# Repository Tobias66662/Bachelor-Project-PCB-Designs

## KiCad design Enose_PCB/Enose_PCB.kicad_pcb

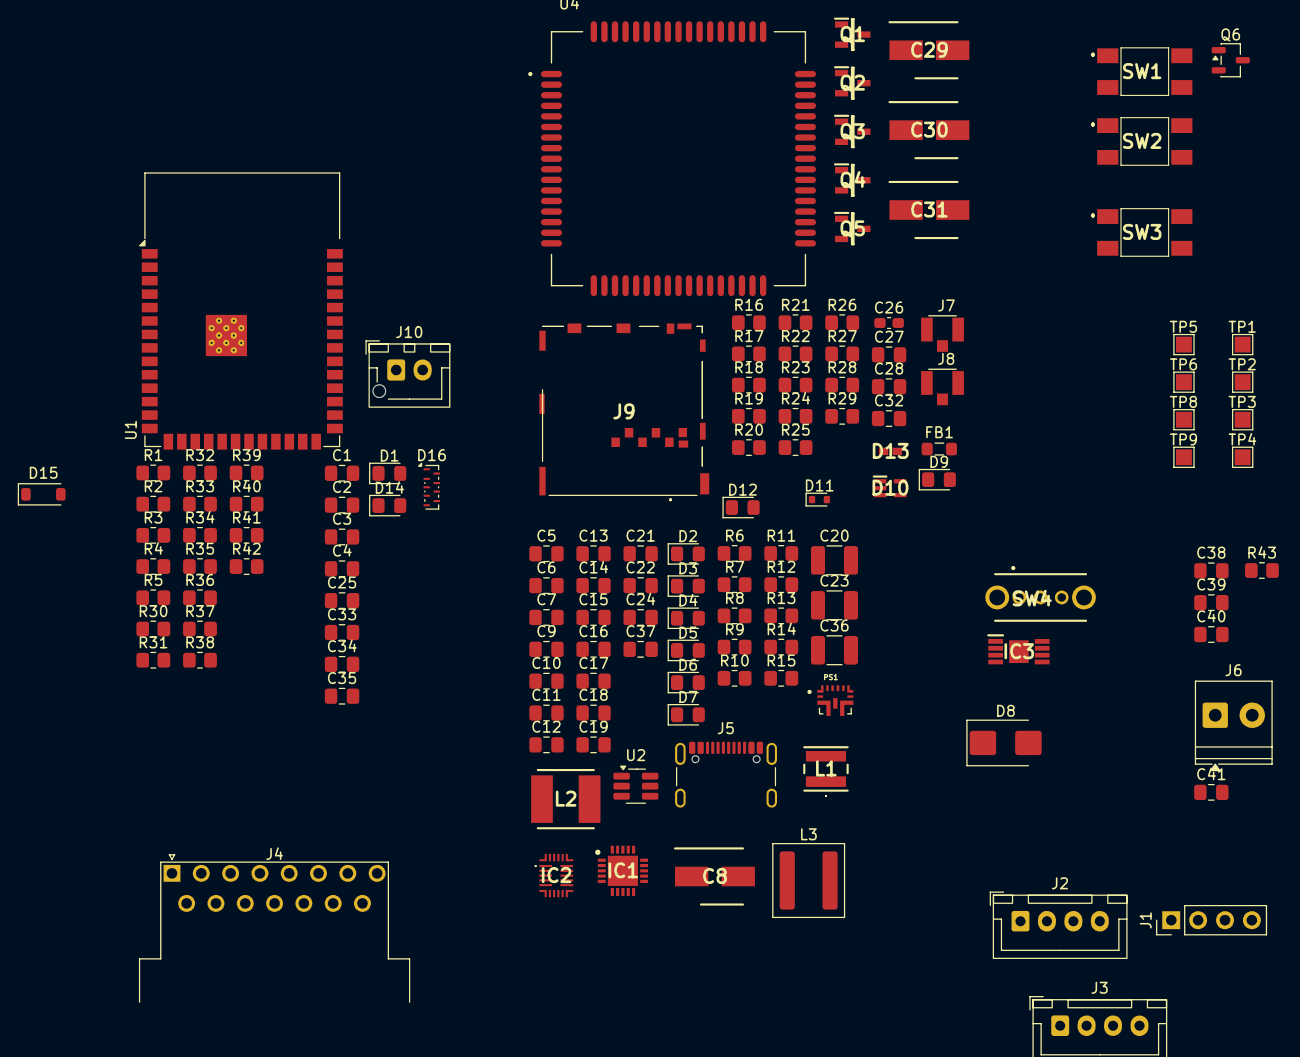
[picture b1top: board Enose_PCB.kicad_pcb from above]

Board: 2 copper layers, 139 parts (0 on the bottom side), 88 nets, no tracks yet.

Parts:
C1, C4, C28: 1u; C_0805_2012Metric_Pad1.18x1.45mm_HandSolder
C2: 22u; C_0805_2012Metric_Pad1.18x1.45mm_HandSolder
C3: 0.1u; C_0805_2012Metric_Pad1.18x1.45mm_HandSolder
C5, C6, C9, C10, C21, C24, C37: 22uF; C_0805_2012Metric_Pad1.18x1.45mm_HandSolder
C7, C11, C13, C17: 10uF; C_0805_2012Metric_Pad1.18x1.45mm_HandSolder
C8: 100uF; CAPAE530X610N
C12, C15: 0.1uF; C_0805_2012Metric_Pad1.18x1.45mm_HandSolder
C14: 22nF; C_0805_2012Metric_Pad1.18x1.45mm_HandSolder
C16, C22, C41: 2.2uF; C_0805_2012Metric_Pad1.18x1.45mm_HandSolder
C18, C38: 1uF; C_0805_2012Metric_Pad1.18x1.45mm_HandSolder
C19: 5.6nF; C_0805_2012Metric_Pad1.18x1.45mm_HandSolder
C20, C23, C36: 22uF; C_1210_3225Metric_Pad1.33x2.70mm_HandSolder
C25, C33, C34, C35, C40: 100nF; C_0805_2012Metric_Pad1.18x1.45mm_HandSolder
C26: 33p; C_0603_1608Metric_Pad1.08x0.95mm_HandSolder
C27, C32: 100n; C_0805_2012Metric_Pad1.18x1.45mm_HandSolder
C29, C30, C31: 100u; CAPAE530X610N
C39: 1500pF; C_0805_2012Metric_Pad1.18x1.45mm_HandSolder
D1, D14: LED Amber; LED_0805_2012Metric_Pad1.15x1.40mm_HandSolder
D2, D3, D9, D12: LED; LED_0805_2012Metric_Pad1.15x1.40mm_HandSolder
D4, D5: LED GREEN; LED_0805_2012Metric_Pad1.15x1.40mm_HandSolder
D6, D7: Amber LED; LED_0805_2012Metric_Pad1.15x1.40mm_HandSolder
D8: SMBJ18A-E3/52; D_SMB
D10: ESDALC6V1W5; SOT65P210X110-5N
D11: ESD5Z5.0T1G; D_SOD-523
D13: 0402ESDA-AEC1; 0402ESDAAEC1
D15: 1N5819; D_SOD-123
D16: DT1240A-08LP3810; UDFN-9_1.0x3.8mm_P0.5mm
FB1: MPZ2012S601AT000; L_0805_2012Metric_Pad1.05x1.20mm_HandSolder
IC1: ISL91127IRNZ-T7A; QFN50P400X400X100-21N
IC2: MP2722GRH-0000-Z; MP2722GRH0000Z
IC3: TPS22958DGNR; SOP65P490X110-9N
J1: Conn_01x04_Pin; PinHeader_1x04_P2.54mm_Vertical
J2, J3: Conn_01x04_Pin; JST_XH_B4B-XH-A_1x04_P2.50mm_Vertical
J4: DA15_Pins; DSUB-15_Pins_Horizontal_P2.77x2.84mm_EdgePinOffset9.40mm
J5: USB_C_Receptacle_USB2.0_16P; USB_C_Receptacle_GCT_USB4105-xx-A_16P_TopMnt_Horizontal
J6: Battery Terminal; TerminalBlock_Phoenix_PT-1,5-2-3.5-H_1x02_P3.50mm_Horizontal
J7, J8: U.FL-R-SMT_01_; HRS_U.FL-R-SMT_01_
J9: 2229333-2; 22293332
J10: Fan; JST_XH_B2B-XH-AM_1x02_P2.50mm_Vertical
L1: 1uH; SRP4030FA1R0M
L2: 1uH; INDPM5355X310N
L3: 4.7uH; L_Coilcraft_XAL6060-XXX
PS1: TPS61288LRQQR; CONV_TPS61288LRQQR
Q1, Q2, Q3, Q4, Q5: Q_NPN; SOT96P237X111-3N
Q6: NMOS; SOT-23-3
R1, R2, R3, R20, R30, R31, R32, R33: 10k; R_0805_2012Metric_Pad1.20x1.40mm_HandSolder
R4, R5, R8: 390; R_0805_2012Metric_Pad1.20x1.40mm_HandSolder
R6: 1k; R_0805_2012Metric_Pad1.20x1.40mm_HandSolder
R7, R25, R29: 680; R_0805_2012Metric_Pad1.20x1.40mm_HandSolder
R9: 6.8k; R_0805_2012Metric_Pad1.20x1.40mm_HandSolder
R10: 10k(1%); R_0805_2012Metric_Pad1.20x1.40mm_HandSolder
R11: 12k; R_0805_2012Metric_Pad1.20x1.40mm_HandSolder
R12: 288k; R_0805_2012Metric_Pad1.20x1.40mm_HandSolder
R13: 75k; R_0805_2012Metric_Pad1.20x1.40mm_HandSolder
R14, R15: 510; R_0805_2012Metric_Pad1.20x1.40mm_HandSolder
R16, R19, R21, R27: 4.7k; R_0805_2012Metric_Pad1.20x1.40mm_HandSolder
R17, R22, R28: 47k; R_0805_2012Metric_Pad1.20x1.40mm_HandSolder
R18: 4.7; R_0805_2012Metric_Pad1.20x1.40mm_HandSolder
R23, R24, R26: 22; R_0805_2012Metric_Pad1.20x1.40mm_HandSolder
R34, R35, R36, R37, R38, R39, R40, R41, R42: 100; R_0805_2012Metric_Pad1.20x1.40mm_HandSolder
R43: 100k; R_0805_2012Metric_Pad1.20x1.40mm_HandSolder
SW1, SW2, SW3: SW_SPST; 430181038816
SW4: SW_SPDT; OS102011MA1QN1
TP1, TP2, TP3, TP4, TP5, TP6, TP8, TP9: TestPoint; TestPoint_Pad_1.5x1.5mm
U1: ESP32-S3-WROOM-1
U2: USBLC6-4SC6; SOT-23-6_Handsoldering
U4: SIM7070G; MODULE_SIM7070G

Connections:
+3V3: C1.1, C2.1, C3.2, C5.2, C6.2, C21.2, C25.2, C33.1, C34.1, C35.1, IC1.15 (FB), IC1.17 (VOUT_1), IC1.18 (VOUT_2), IC1.19 (VOUT_3), IC1.20 (VOUT_4), IC1.21 (EPAD), J1.4, J2.4, J3.4, Q6.1 (D), R1.1, R2.1, R3.1, R8.1, R31.2, R32.1, R33.2, TP1.1, U1.2 (3V3)
+15V: C20.1, C23.1, C36.1, D8.1 (A1), J4.7, J4.8, J4.15, PS1.5 (VOUT), R9.1, R11.1, TP4.1
+BATT: C7.1, C11.1, C12.1, C40.2, D9.2 (A), D11.1 (A1), D12.2 (A), FB1.2, IC1.6 (PVIN_1), IC1.7 (PVIN_2), IC1.8 (PVIN_3), IC1.9 (PVIN_4), IC1.10 (VIN), IC1.11 (EN), IC3.5 (VOUT_1), IC3.8 (VOUT_2), L3.1, PS1.7 (VIN)
+SYS: C8.1, C9.1, C10.2, C37.1, C38.2, IC2.13 (SYS), IC3.1 (VIN_1), IC3.3 (VBIAS), IC3.4 (VIN_2), L2.1, R7.1, R43.2, TP2.1
/Cellular Module/GNSS_ANT: J7.3 (SIG), U4.53 (GNSS_ANT)
/Cellular Module/NETLIGHT: R27.1, U4.52 (NETLIGHT)
/Cellular Module/RF_ANT: D13.2 (A2), J8.3 (SIG), U4.60 (RF_ANT)
/Cellular Module/SIM_CLK: R24.2, U4.32 (SIM_CLK)
/Cellular Module/SIM_DATA: R23.2, U4.31 (SIM_DATA)
/Cellular Module/SIM_RST: R26.1, U4.33 (SIM_RST)
/Cellular Module/SIM_VDD: C32.2, D10.5 (K), J9.1 (VCC), U4.30 (SIM_VDD)
/Cellular Module/STATUS: R21.1, U4.66 (STATUS)
/Cellular Module/VDD_EXT: R18.1, R19.1, R20.2, TP9.1, U4.15 (VDD_EXT)
/EN: C4.1, R1.2, R3.2, SW1.4 (B), U1.3 (EN)
/ESP_LED1: R4.1, U1.6 (IO6)
/ESP_LED2: R5.1, U1.7 (IO7)
/Fan PWM: R34.2, U1.12 (IO8)
/PWM1: R35.1, U1.17 (IO9)
/PWM2: R36.1, U1.18 (IO10)
/PWM3: R37.1, U1.19 (IO11)
/PWM4: R38.1, U1.20 (IO12)
/PWM5: R39.1, U1.21 (IO13)
/PWM6: R40.1, U1.22 (IO14)
/PWM7: R41.1, U1.8 (IO15)
/PWM8: R42.1, U1.9 (IO16)
/Power Components/BATT: C24.2, IC2.12 (BATTSNS), IC2.14 (BATT), J6.1
/Power Components/BST: C14.2, IC2.6 (BST_1), IC2.24 (BST_2)
/Power Components/CC1: IC2.1 (CC1), J5.A5 (CC1), U2.1 (I/O1)
/Power Components/CC2: IC2.22 (CC2_1), IC2.23 (CC2_2), J5.B5 (CC2), U2.3 (I/O2)
/Power Components/NTC1: IC2.10 (NTC1), R10.1, TP3.1
/Power Components/PG/NTC2: D6.1 (K), IC2.9 (PG/_NTC2)
/Power Components/STAT/IB: D7.1 (K), IC2.11 (STAT/_IB_1), IC2.25 (STAT/_IB_2)
/Power Components/VCC: C22.1, C41.1, IC2.19 (VCC), R14.1, R15.1
/Power Components/VRNTC: IC2.7 (VRNTC), R10.2
/Power Components/~RST: IC2.17 (~RST_1), IC2.26 (~RST_2), SW3.1 (A)
EN(15V): PS1.6 (EN), U1.11 (IO18)
GND: C1.2, C2.2, C3.1, C4.2, C5.1, C6.1, C7.2, C8.2, C9.2, C10.1, C11.2, C12.2, C13.2, C16.2, C17.2, C18.1, C20.2, C21.1, C22.2, C23.2, C24.1, C25.1, C26.1, C27.1, C28.1, C29.2, C30.2, C31.2, C32.1, C33.2, C34.2, C35.2, C36.2, C37.2, C38.1, C39.2, C40.1, C41.2, D1.1 (K), D2.1 (K), D3.1 (K), D4.1 (K), D5.1 (K), D8.2 (A2), D10.2 (A), D11.2 (A2), D13.1 (A1), D14.1 (K), D15.2 (A), D16.3 (A), IC1.3 (PGND), IC1.12 (MODE), IC1.13 (SGND_1), IC1.14 (SGND_2), IC2.5 (PGND), IC2.18 (AGND), IC3.6 (GND), IC3.9 (EP), J1.3, J2.3, J3.3, J4.5, J4.6, J4.13, J4.14, J5.A1 (GND), J5.A12 (GND), J5.B1 (GND), J5.B12 (GND), J5.S1 (SHIELD), J6.2, J7.1 (GND), J7.2 (GND), J8.1 (GND), J8.2 (GND), J9.4 (GND_1), J9.8 (GND_2), J9.9 (GND_3), J9.10 (GND_4), J9.11 (GND_5), J9.12 (GND_6), J9.13 (GND_7), J9.14 (GND_8), J9.15 (GND_9), J9.16 (GND_10), J9.17 (GND_11), J10.2, PS1.3 (PGND), PS1.10 (AGND), R12.2, R13.2, R17.1, R22.1, R28.1, R30.2, SW1.1 (A), SW2.1 (A), SW3.4 (B), SW4.2 (B), U1.1 (GND), U1.40 (GND), U1.41 (GND), U2.2 (GND), U4.2 (GND), U4.17 (GND__1), U4.18 (GND__2), U4.29 (GND__3), U4.39 (GND__4), U4.45 (GND__5), U4.46 (GND__6), U4.54 (GND__7), U4.58 (GND__8), U4.59 (GND__9), U4.61 (GND__10), U4.62 (GND__11), U4.63 (GND__12), U4.64 (GND__13), U4.65 (GND__14)
I2C_SCL: IC2.15 (SDA), J1.2, J2.2, J3.2, R31.1, U1.27 (IO0)
I2C_SDA: IC2.16 (SCL), J1.1, J2.1, J3.1, R32.2, U1.39 (IO1)
unnamed: C15.1, L3.2, PS1.4 (SW), PS1.9 (SW)
unnamed: C19.2, R13.1
unnamed: D1.2 (A), R4.2
unnamed: D2.2 (A), R6.2
unnamed: D3.2 (A), R7.2
unnamed: D4.2 (A), R8.2
unnamed: D5.2 (A), R9.2
unnamed: D6.2 (A), R14.2
unnamed: D7.2 (A), R15.2
unnamed: D9.1 (K), R25.1
unnamed: D12.1 (K), R29.1
unnamed: D14.2 (A), R5.2
unnamed: D15.1 (K), J10.1, Q6.3 (S)
unnamed: D16.1 (K1), J4.1, R42.2
unnamed: D16.2 (K2), J4.9, R41.2
unnamed: D16.4 (K3), J4.2, R40.2
unnamed: D16.5 (K4), J4.10, R39.2
unnamed: D16.6 (K5), J4.3, R38.2
unnamed: D16.7 (K6), J4.11 (P111), R37.2
unnamed: D16.8 (K7), J4.4, R36.2
unnamed: D16.9 (K8), J4.12, R35.2
unnamed: IC1.4 (LX1_1), IC1.5 (LX1_2), L1.2
unnamed: IC1.1 (LX2_1), IC1.2 (LX2_2), L1.1
unnamed: C13.1, IC2.3 (PMID)
unnamed: C14.1, IC2.4 (SW), L2.2
unnamed: C39.1, IC3.7 (CT)
unnamed: IC3.2 (ON), R43.1, SW4.1 (A)
unnamed: D10.3 (K), J9.3 (CLK), R24.1
unnamed: D10.1 (K), J9.6 (I/O), R23.1
unnamed: D10.4 (K), J9.2 (RST), R26.2
unnamed: C15.2, PS1.8 (BST)
unnamed: C19.1, PS1.2 (COMP)
unnamed: PS1.1 (FB), R11.2, R12.1
unnamed: C16.1, PS1.11 (VCC)
unnamed: R16.2, R17.2
unnamed: R21.2, R22.2
unnamed: R27.2, R28.2
unnamed: Q6.2 (G), R30.1, R34.1
unnamed: SW2.4 (B), U1.15 (IO3)
unnamed: TP6.1, U4.22 (DEBUG_RXD)
unnamed: TP5.1, U4.23 (DEBUG_TXD)
unnamed: C26.2, R20.1, U4.10 (UART1_RXD)
unnamed: C27.2, C28.2, C29.1, C30.1, C31.1, FB1.1, TP8.1, U4.55 (VBAT), U4.56 (VBAT__1), U4.57 (VBAT__2)
PWRKEY: R16.1, U1.10 (IO17)
UART1_TXD: R2.2, U1.36 (RXD0)
USB_D+: J5.A6 (D+), J5.B6 (D+), U1.14 (USB_D+/IO20), U2.6 (I/O4)
USB_D-: J5.A7 (D-), J5.B7 (D-), U1.13 (USB_D-/IO19), U2.4 (I/O3)
VBUS: C17.1, C18.2, IC2.2 (IN), J5.A4 (VBUS), J5.A9 (VBUS), J5.B4 (VBUS), J5.B9 (VBUS), R6.1, U2.5 (VBUS)
~INT: IC2.8 (~INT), R33.1, U1.38 (IO2)

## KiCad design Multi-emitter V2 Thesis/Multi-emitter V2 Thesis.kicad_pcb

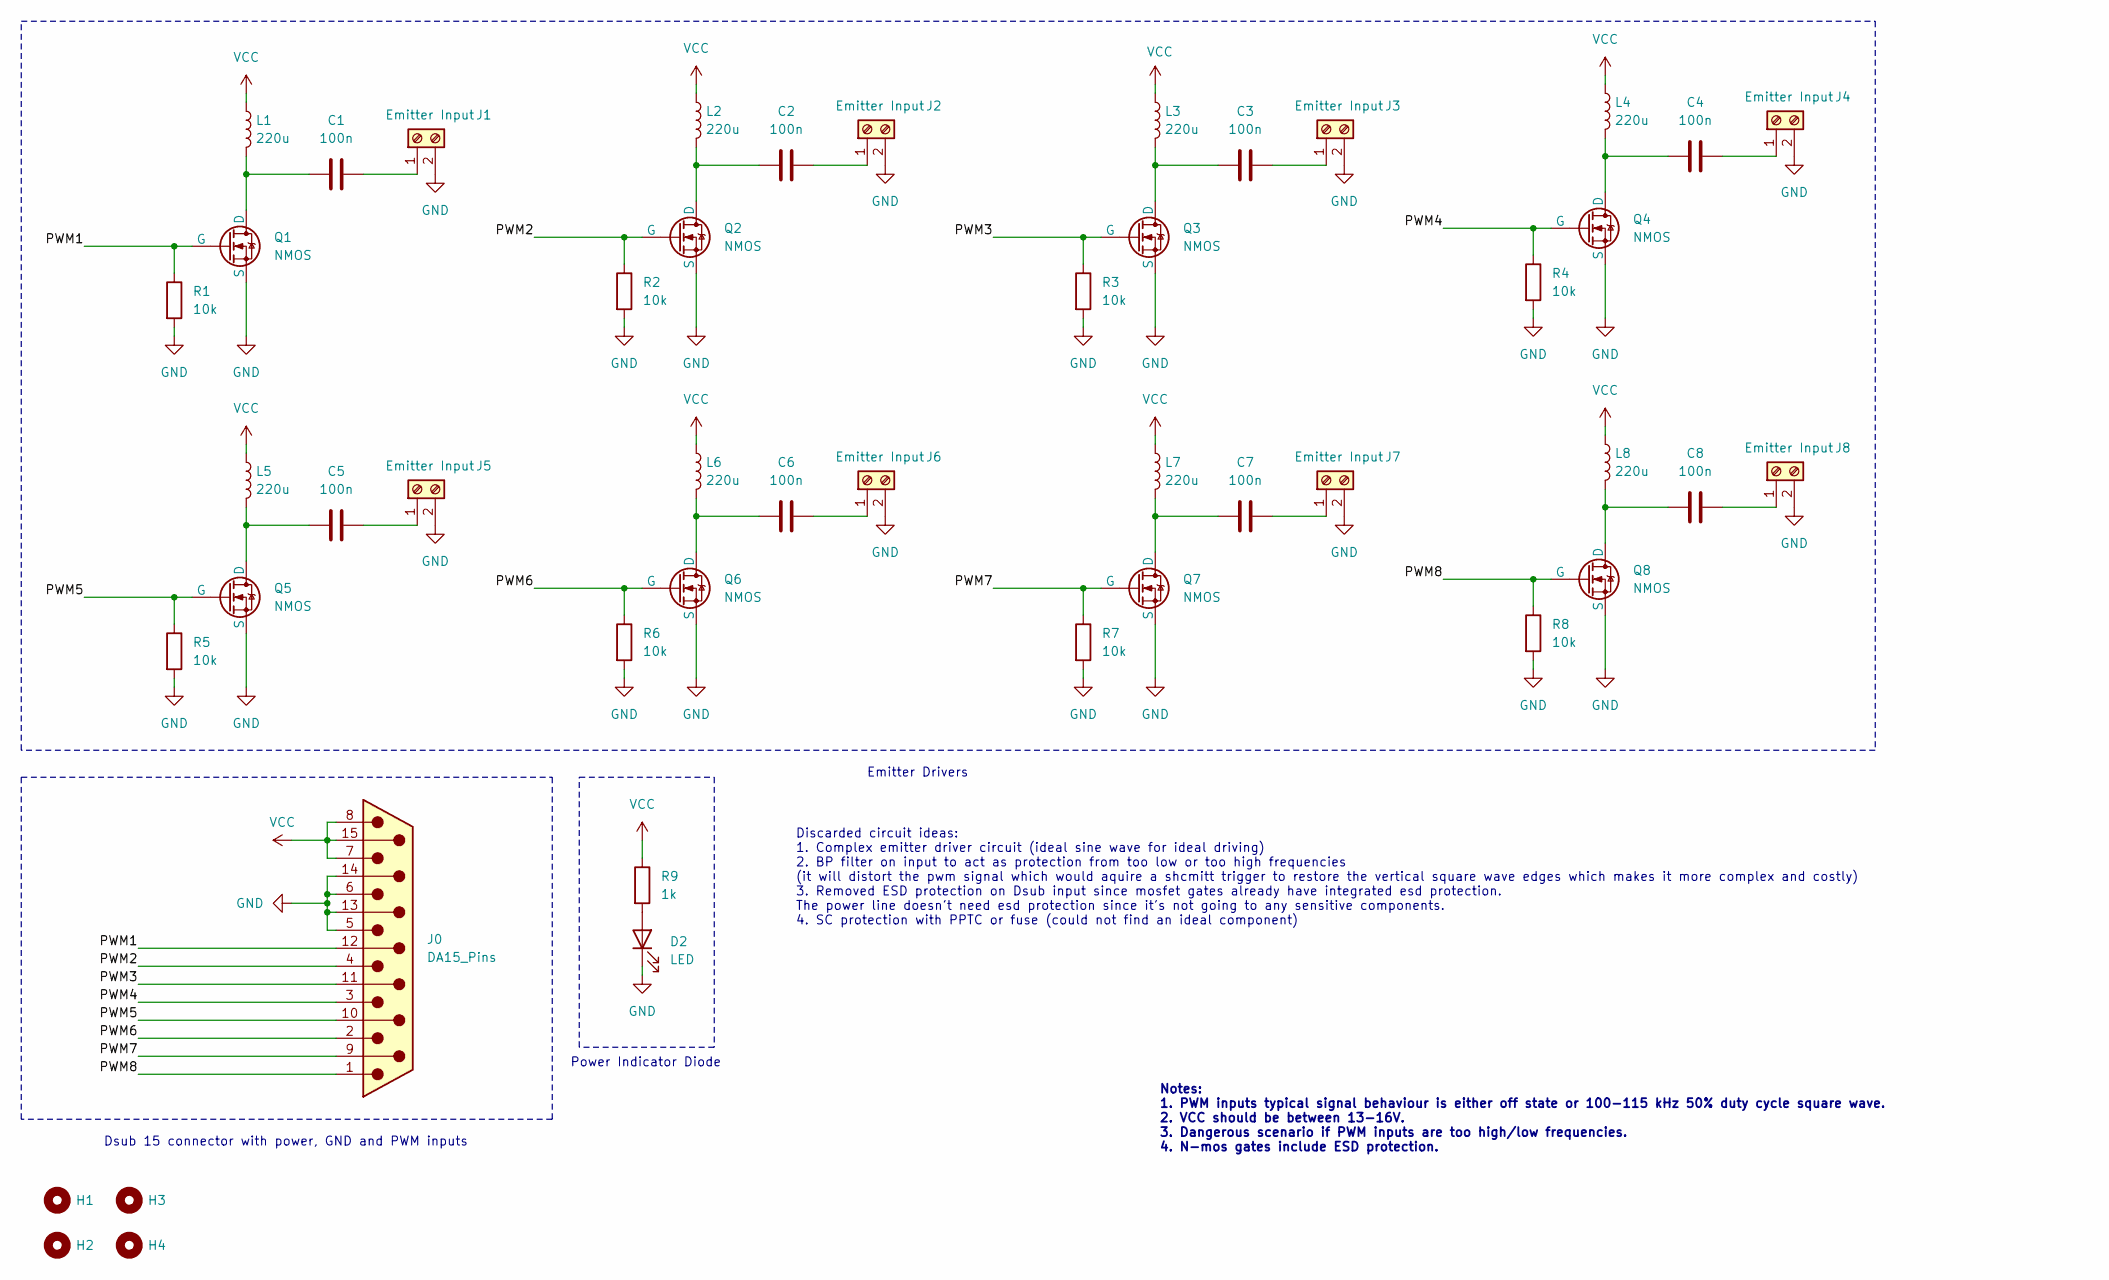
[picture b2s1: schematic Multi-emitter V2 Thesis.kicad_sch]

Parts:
C1, C2, C3, C4, C5, C6, C7, C8: 100n; C_0805_2012Metric_Pad1.18x1.45mm_HandSolder
D2: LED; LED_D5.0mm
H1, H2, H3, H4: MountingHole; MountingHole_3.2mm_M3_DIN965_Pad
J0: DA15_Pins; XM3B1522112
J1, J2, J3, J4, J5, J6, J7, J8: Emitter Input; JST_PH_S2B-PH-K_1x02_P2.00mm_Horizontal
L1, L2, L3, L4, L5, L6, L7, L8: 220u; INDPM102100X400N
Q1, Q2, Q3, Q4, Q5, Q6, Q7, Q8: NMOS; Ventsi_SOT23
R1, R2, R3, R4, R5, R6, R7, R8: 10k; R_0805_2012Metric_Pad1.20x1.40mm_HandSolder
R9: 1k; R_0805_2012Metric_Pad1.20x1.40mm_HandSolder

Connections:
/PWM1: J0.12, Q1.2 (G), R1.1
/PWM2: J0.4, Q2.2 (G), R2.1
/PWM3: J0.11 (P111), Q3.2 (G), R3.1
/PWM4: J0.3, Q4.2 (G), R4.1
/PWM5: J0.10, Q5.2 (G), R5.1
/PWM6: J0.2, Q6.2 (G), R6.1
/PWM7: J0.9, Q7.2 (G), R7.1
/PWM8: J0.1, Q8.2 (G), R8.1
GND: D2.1 (K), J0.5, J0.6, J0.13, J0.14, J1.2, J2.2, J3.2, J4.2, J5.2, J6.2, J7.2, J8.2, Q1.3 (S), Q2.3 (S), Q3.3 (S), Q4.3 (S), Q5.3 (S), Q6.3 (S), Q7.3 (S), Q8.3 (S), R1.2, R2.2, R3.2, R4.2, R5.2, R6.2, R7.2, R8.2
unnamed: D2.2 (A), R9.2
unnamed: C1.2, J1.1
unnamed: C2.2, J2.1
unnamed: C3.2, J3.1
unnamed: C4.2, J4.1
unnamed: C5.2, J5.1
unnamed: C6.2, J6.1
unnamed: C7.2, J7.1
unnamed: C8.2, J8.1
unnamed: C1.1, L1.2, Q1.1 (D)
unnamed: C2.1, L2.2, Q2.1 (D)
unnamed: C3.1, L3.2, Q3.1 (D)
unnamed: C4.1, L4.2, Q4.1 (D)
unnamed: C5.1, L5.2, Q5.1 (D)
unnamed: C6.1, L6.2, Q6.1 (D)
unnamed: C7.1, L7.2, Q7.1 (D)
unnamed: C8.1, L8.2, Q8.1 (D)
VCC: J0.7, J0.8, J0.15, L1.1, L2.1, L3.1, L4.1, L5.1, L6.1, L7.1, L8.1, R9.1

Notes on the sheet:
Notes: 1. PWM inputs typical signal behaviour is either off state or 100-115 kHz 50% duty cycle square wave. 2. VCC should be between 13-16V. 3. Dangerous scenario if PWM inputs are too high/low frequencies. 4. N-mos gates include ESD protection.
Emitter Drivers
Dsub 15 connector with power, GND and PWM inputs
Discarded circuit ideas: 1. Complex emitter driver circuit (ideal sine wave for ideal driving) 2. BP filter on input to act as protection from too low or too high frequencies (it will distort the pwm signal which would aquire a shcmitt trigger to restore the vertical square wave edges which makes i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
Power Indicator Diode

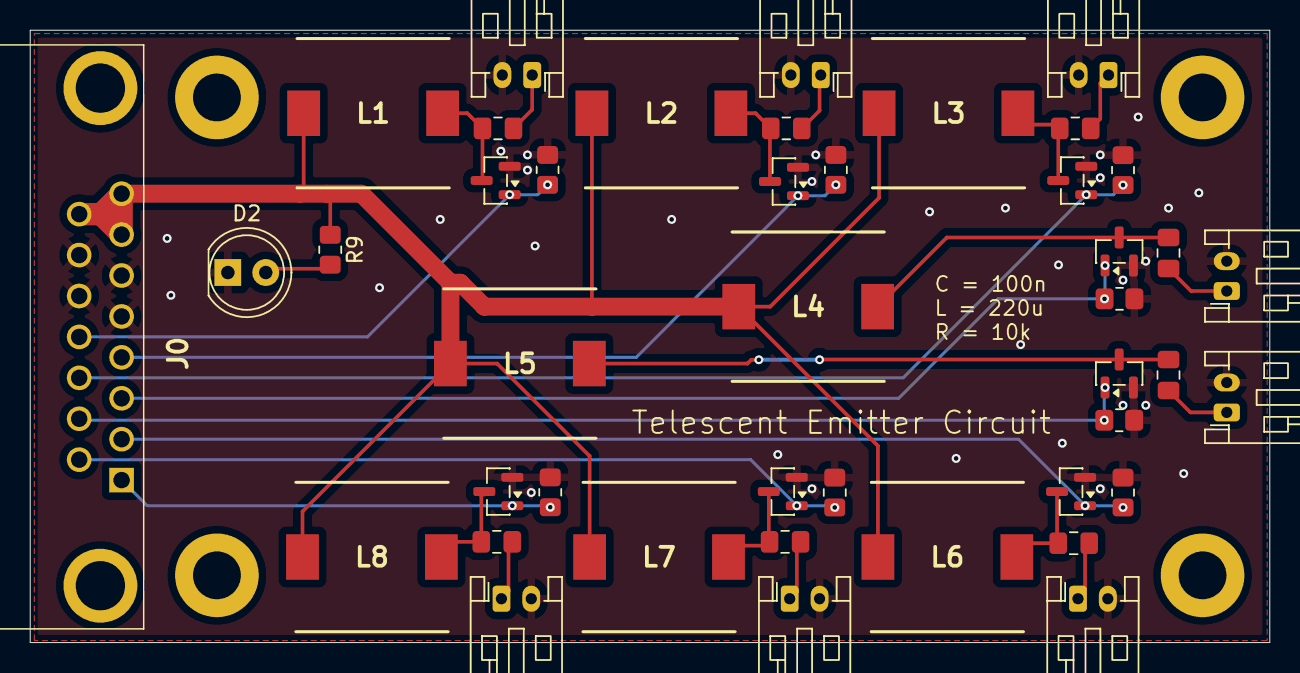
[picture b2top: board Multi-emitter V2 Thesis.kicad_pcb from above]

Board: 2 copper layers, 83.0 x 41.0 mm, 47 parts (0 on the bottom side), 27 nets.

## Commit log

2026-02-19 inital commit
2026-02-24 Worked on the Schematic for the modem
2026-03-01 Added Power Components
2026-03-08 Updated component values
2026-03-08 redoing footprints
2026-03-08 adding fan power to main pcb
2026-03-09 adding fan control circuitry
2026-03-09 assigning gpi06 to control fan
2026-03-09 PCB layout done on emitter PCB - ready to order
2026-03-11 Added LED
2026-03-11 Changed Battery Charger
2026-03-11 Added some fancy silkscreen text and generated gerber files
2026-03-13 Added load switch and stuff
2026-03-14 Assigned footprints
